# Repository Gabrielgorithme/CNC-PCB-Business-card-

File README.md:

# Hybrid business card: milled aluminium + PCB

The second version of Gabriel Ghanem's CNC business card. One half is milled from 7075 aluminium on a hobby CNC,
the other is a four-layer circuit board, and the two meet along a ripple that spreads from the card's flexure.

| | |
|---|---|
|  |  |

- Card: 85.60 x 53.98 x 1.70 mm, corners R3.18.
- Aluminium half: 7075, engraved both faces, with the same flexure as the first card.
- Board half: 1.2 mm, black mask, gold finish, castellated holes on the free edge. It carries an NFC tag
  (NT3H2111): a phone held to the card opens the website, and the phone's field lights a red LED behind a slot
  in the board. There is no battery.
- Joint: the board sits in a pocket on a narrow ledge, located by two pins milled from the solid, flush with the
  ripple crests.

## Where things are

| Folder | What it holds |
|---|---|
| `design/hybrid/` | The mockups that set the look. `concept_b2.py` is the chosen direction ("Wavefront"). |
| `pcb/revA/` | The board, generated by Python scripts as a KiCad project. `out/order/` is the package for the fab: Gerbers, BOM, placement. |
| `cad/hybrid/` | The aluminium half as a STEP model, generated with CadQuery from the same numbers as the board, plus the fit gauge and the drawing of the joint (`interface.png`). |
| `lettering/` | The single-line ISOCP letters, as engraved on the first card. |

Each folder has its own README with the details: geometry and checks for the board in `pcb/revA/`, how the board
is held and what gets machined to the delivered boards in `cad/hybrid/`.

## Status

Rev A. The board has been through an independent audit and a pre-order review; both are recorded in
`pcb/revA/README.md`. The aluminium pocket is cut to the measured thickness of the delivered boards
(`python3 cad/hybrid/build_alu.py --board-t <measured>`), so the aluminium half is finalised once boards are in hand.

## Rebuilding

- Mockups: `python3 design/hybrid/generate.py b2` (numpy, pillow, shapely, segno, `rsvg-convert`).
- Board: `pcb/revA/build.sh` (KiCad's Python module `pcbnew` and `kicad-cli`, shapely, numpy, pillow, scipy, CadQuery).
  A rebuild rewrites the Gerber zip with new time stamps even when nothing changed.
- Aluminium: `python3 cad/hybrid/build_alu.py` (CadQuery, svgelements; `--engrave` adds the engraved model).

## The first card

The first card (all aluminium) and the website both cards point to are in
[CNC-Business-card-](https://github.com/Gabrielgorithme/CNC-Business-card-). The QR code on both cards opens
https://gabrielgorithme.github.io/CNC-Business-card-/, which is served from that repository.

The history of this repository starts on that repository's branch `claude/hybrid-card-mockups`; the commits were
moved here unchanged on 2026-11-25.

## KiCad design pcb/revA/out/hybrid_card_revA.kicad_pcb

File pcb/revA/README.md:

# Hybrid card, PCB half, rev A

The board half of the B2 "Wavefront" card, generated from the same numbers as the mockup in `design/hybrid/`.
Rev A is ordered as the production batch (20 to 40 cards), not as a test coupon first: antenna tuning, the one thing
that cannot be settled on paper, is done by hand on the batch through the solder bridges.

## What is in `out/`

| File | What it is |
|---|---|
| `hybrid_card_revA.kicad_pcb` / `.kicad_pro` | The board. Written in KiCad 7's format, which KiCad 10 opens. |
| `gg_card.pretty/`, `fp-lib-table` | Project footprint library (the chip's footprint). |
| `hybrid_card_revA_board.step` | 3D model of the board with its parts, in the card's CAD frame (see below). For the assembly with the aluminium half. |
| `preview_front.jpg`, `preview_back.jpg`, `preview_front_lit.jpg` | Previews composited from KiCad's own layer plots. The back is shown as seen from the back. The lit view is a model, not a measurement. |
| `hybrid_card_revA_BOM_JLC.csv`, `..._CPL_JLC.csv` | Assembly files in JLCPCB's column layout (draft). |
| `order/` | What goes to JLCPCB: `hybrid_card_revA_gerbers.zip` (4 copper layers, masks, pastes, silkscreens, outline, one plated drill file: 87 x 0.3, 8 x 0.8, 2 x 2.1), the BOM and the placement file. Written by `make_order.py`. |
| `decal_front.jpg`, `decal_back.jpg` | The same pictures cropped exactly to the board's bounding box (43.565 x 47.42 mm, 54 px/mm), to lay on the 3D model's faces. The back one is as seen from the back. |

## Geometry shared with the aluminium half (card frame, mm, origin = card top-left seen from the recto)

- Flexure / ripple centre (19.0, 21.5). Joint on the 18th ripple crest, R36.
- Rims 3.18 top and bottom. Ledge 4.0 along the joint, 1.5 under the rims.
- Board outline drawn 0.10 smaller than the nominal pocket per side, R1.0 on the corners that sit in the pocket.
  The pocket is meant to be machined to the delivered boards.
- Two locating pins at R38, -24 deg and +22 deg: (53.71, 6.04) and (54.23, 35.74). Plated holes 2.10, lands 2.80.
- The free edge stops 0.10 inside the card's edge (x = 85.50).
- Copper to edge: on the back, along the joint and the rims, nothing closer than 0.50 (the pin lands). On the front the
  gold rings come to 0.36 and the edge fingers to 0.30 of the free edge.
- How the board sits on the aluminium (seat, glue land, pins, heights) is in `cad/hybrid/README.md`.

## The tag

NT3H2111 (NTAG I2C plus, 50 pF input capacitance, energy-harvesting output). VOUT feeds 220 nF, then 33 ohm and a red LED
(a standard top-emitting 0402 on the back). The resistor only matters in a strong field; 33 ohm is in JLCPCB's basic list.
Antenna: 7-turn rectangular spiral on the back, 14.1 x 29.2 mm, 0.20 track / 0.15 gap, placed against the board's free
edge, away from the aluminium. Calculated free-air inductance 2.10 uH (`coil.py`, Greenhouse method; expect about 10 % error).

It is deliberately tuned high. Three C0G capacitors sit behind solder bridges JP1..JP3: two bare pads 0.25 apart under one
mask opening, no paste. A blob of solder closes one; wick opens it again.

| Bridges closed | Added | Tunes this inductance to 13.56 MHz | Resonance if L = 2.10 uH |
|---|---|---|---|
| none | 0 pF | 2.65 uH | 15.2 MHz |
| JP1 | 6.8 pF | 2.34 uH | 14.3 MHz |
| JP2 | 12 pF | 2.15 uH | 13.7 MHz |
| JP1+JP2 | 18.8 pF | 1.95 uH | 13.1 MHz |
| JP3 | 22 pF | 1.86 uH | 12.8 MHz |
| JP1+JP3 | 28.8 pF | 1.70 uH | 12.2 MHz |
| JP2+JP3 | 34 pF | 1.60 uH | 11.8 MHz |
| all | 40.8 pF | 1.48 uH | 11.4 MHz |

Aluminium next to the coil lowers its inductance, so the right combination is found with the board seated in a pocket:
try the combinations and keep the one with the longest read range and brightest LED.

## Decorative copper

The BGA land pattern, fan-out, castellations, edge fingers, meanders and test points connect to nothing.
Each trace with the pads it touches is its own small net (`ART_1` ... `ART_68`), so the design-rule check treats them as
intended connections and still checks their clearances.

## Hidden under the ledge (back)

- Copper text at 0.5 / 0.6 / 0.7 / 0.8 / 1.0 mm and lines at 0.10 / 0.127 / 0.15 / 0.20 / 0.25 mm: a record of what this
  fab resolves, for the next board. Nothing on the board is under 0.10.

Nothing on the board is left to chance against the fab's limits any more: the antenna is fully under mask, and in the BGA
field the lands are gold while the dog-bone vias stay under mask on both faces, as on a real BGA: the gold neck of each
dog-bone stops at the via pad's edge, so the fab plugs all 49 holes and no mask web there is under 0.254.

## Vernier (back)

Eleven gold ticks 1.35 deg apart just outside the ledge's edge, facing eleven ticks 1.50 deg apart engraved on the aluminium.
One step of coincidence is 0.1 mm at R40.

## 3D model

`hybrid_card_revA_board.step` uses the same frame as `cad/build_card.py`: X along the long edge, Y up as seen from the
recto, origin at the card's bottom-left corner, Z = 0 the verso face, Z = 1.70 the faced recto. The board's top face
is at ripple-crest height, Z = 1.68; a 1.20 board occupies Z = 0.48 ... 1.68. Dropped into the card's assembly at the
origin it is in place.

The outline is rebuilt from true lines and arcs. Vias and copper are not modelled. Part bodies are plain blocks
(chip 1.6 x 1.6 x 0.5 from the datasheet; 0402 heights are nominal catalogue values).

## Thickness: 1.2 mm board

Card 1.70, board 1.20 nominal. The pocket is cut to the measured thickness of the delivered boards, so the top face
lands at crest height whatever the fab delivers (their tolerance is 10 %). The parts on the back are 0.50 tall:
with a 1.20 board their lowest face is 0.02 below the verso plane, plus the solder under them.
The stack-up in the board file is a nominal split that adds up to 1.20; the fab's standard 1.2 mm 4-layer stack-up applies.

## Checks done

- Design-rule check in KiCad 10.0.8 (through kicad-mcp-pro on the PC) and in KiCad 7: same result both times,
  0 unconnected items, 0 courtyard issues, 8 violations. All 8 are the castellated half-holes sitting on the
  board edge, which is what a castellated hole is.
- Rendered from the plots and looked at, front, back and lit.
- 3D model against KiCad's own STEP export of the board: same bounding box, same thickness, outline area equal to the
  board file's polygon to 0.01 mm2. Volumes differ by 7 mm3, which is the vias.
- Chip footprint against figs. 31 (outline) and 32 (reflow footprint) of the NT3H2111_2211 data sheet, rev 3.6, looked at as
  drawings: terminal order, land size and position, the wider pin 1 land and the bare centre all match. The paste is deliberately not the data sheet's: see the pre-order
  review below.
- Unused chip pins: SCL, SDA and FD are left open and VCC is not connected. NXP's support answers on their community
  forum say these may float when unused.
- Part numbers (JLCPCB parts library, looked up 2026-11-25): U1 C710403, D1 C130719 (NationStar NCD0402R1, red),
  R1 C25105 (33 ohm), C2 C16772 (220 nF X7R 16 V), C3 C1576 (6.8 pF C0G), C4 C1547 (12 pF C0G), C5 C1555 (22 pF C0G).
  Stock was not checked.

## Audit (2026-11-25)

An independent audit of the board file rebuilt the connectivity from the copper alone: all eight intended connections of
the tag circuit pass, no shorts, no opens, no closed copper loop over the coil on any layer, inductance confirmed at
2.09 to 2.10 uH by a second method. Its findings and what was done:

| Finding | Done |
|---|---|
| Placement angles were KiCad's raw bottom-side values; JLCPCB reads the bottom mirrored | `make_assembly.py` writes 180 minus KiCad's angle |
| No pin 1 mark for U1 on silk, D1's cathode dot too small to print | 0.4 dots beside U1 pin 1 and D1's cathode |
| Pin 1 land and paste of U1 not confirmed against the drawing | Redrawn from figs. 31 and 32 as seen: every land 0.40 x 0.22 at 0.60 from centre, the pin 1 land 0.32 wide with the extra 0.10 towards the corner. The 0.10 toe added earlier is gone. Paste: see the pre-order review |
| Castellations: 0.15 ring, first hole 2.32 from the corner | Pads 1.3 high (0.25 ring), row moved down 0.7 (3.02 from the corner) |
| A width clamp made every ladder line 0.15 | Ladders bypass the clamp |
| Mask webs under 0.254 at the pin lands and in the BGA field | Ring ends pulled back from the pin lands (0.3 web); dog-bone vias now under mask |
| 0.10 ring on the 49 dog-bone vias | 0.6 pads (0.15 ring) |
| "No copper within 0.6 of any edge" was not true | Statement corrected above |
| Solder bridges were 0402 lands with paste and a mask dam | Proper open solder bridges |
| "U1" label touched the layer-marker window | Moved |

## Pre-order review (2026-11-25)

A second pass by the same auditor on the order package and the JLCPCB cart, before payment. One blocking item, two cosmetic:

| Finding | Done |
|---|---|
| U1 paste apertures 0.35 x 0.17 (the data sheet's 0.025 pull-back): area ratio 0.57 with a 0.10 stencil, 0.48 with the 0.12 that JLCPCB pairs with 0402 and 0.5 pitch. Under the 0.66 guideline | Paste on the full land, 0.40 x 0.22 on all eight terminals (0.71 and 0.59), pin 1's at the nominal position with none on its extra strip |
| `JLCJLCJLCJLC` placeholder on silk: the auditor reads JLCPCB's help page as saying the order-number mark was withdrawn in 2026 and the placeholder should be left off; with "Remove Mark" it would print as written | Removed |
| The mask opening of each dog-bone ran to the via centre: 43 % of the hole open on the front, so neither plugged nor open | Opening ends at the via pad's edge; the 49 vias are covered on both faces |

Checked against the package uploaded before: only the back paste, back silk and front mask layers differ, and only at
those three places (rendered at 0.01 mm per pixel). Copper, outline and drill are identical.

## Before ordering

1. **Placement preview.** The angles are now converted for the bottom side, but JLCPCB also applies its own offset per
   library part. In their preview, U1's pin 1 must sit by the silk dot at (65.40, 42.80) and D1's cathode by the dot at
   (63.71, 37.90), card frame.
2. **Tooling holes.** Economic assembly may add tooling holes where JLCPCB chooses. Check that option, and the edge-rail
   option, at quote.
3. **LED direction.** A standard LED on the back shines away from the board. Whether enough light comes back into the
   slot off the phone is what this coupon tests.

## Order options this design assumes

| Option | Choice |
|---|---|
| Layers, thickness | 4 layers, 1.2 mm |
| Solder mask, finish | Black, ENIG |
| Castellated holes | Yes, 1 edge |
| Via covering | Plugged: the tented vias get filled, every hole with a mask opening stays open and gold |
| Outline tolerance | The precision option (+/-0.1) if offered |
| Mark on PCB (order number) | Remove Mark. No placeholder text on the board |
| Confirm production file / parts placement | Yes to both: this is where a rotated U1 or D1 gets caught |
| Assembly | Bottom side only; JP1..JP3 are not parts |
| Panel, rails, tooling holes | The curved edge and the castellated edge must stay clean. If the fab needs tabs or mouse-bites, ask for them on the two straight edges only (y = 3.28 and y = 50.70) |

## Rebuild

`./build.sh` (needs KiCad's Python module `pcbnew`, `kicad-cli`, shapely, numpy, scipy, pillow, `rsvg-convert`;
`make_step.py` needs CadQuery and runs without KiCad).

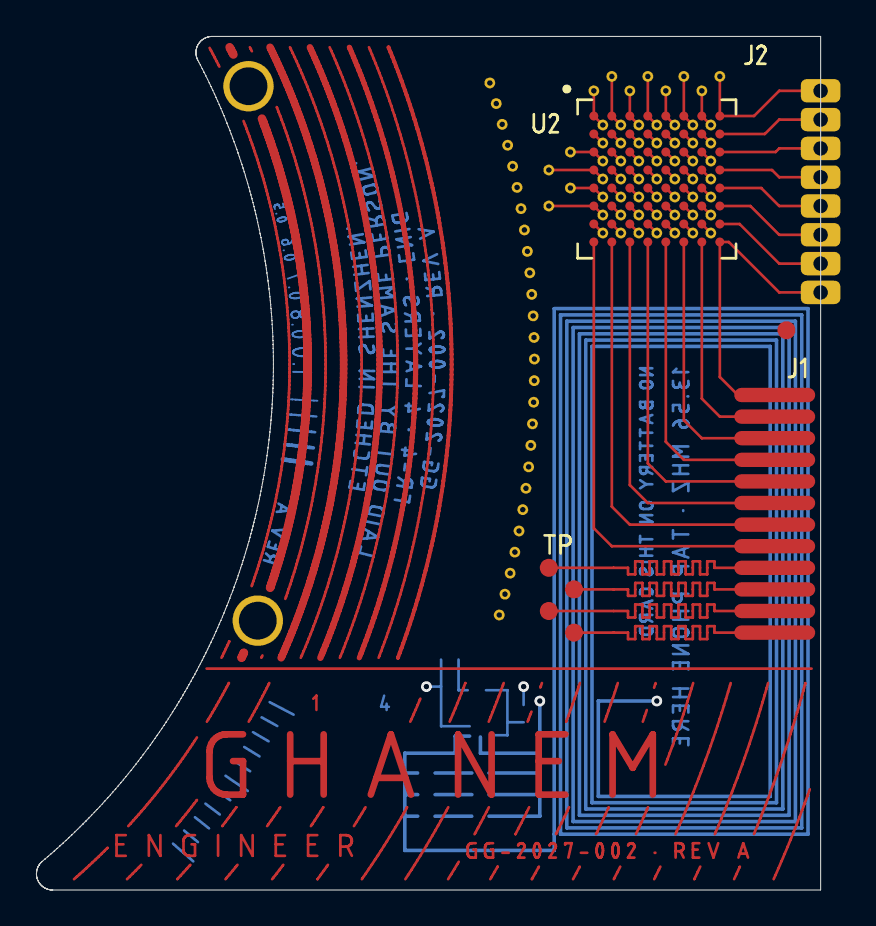
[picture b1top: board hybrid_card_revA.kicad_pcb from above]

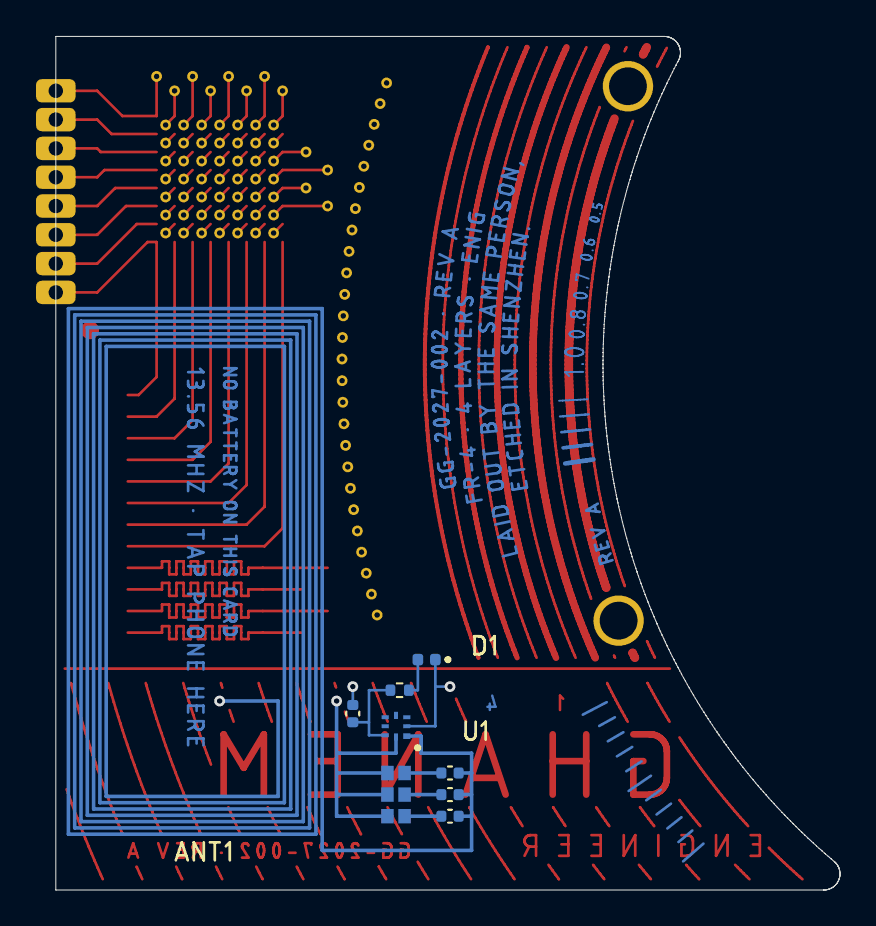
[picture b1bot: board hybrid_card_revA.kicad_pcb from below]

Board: 4 copper layers, 43.6 x 47.4 mm, 12 parts (11 on the bottom side), 76 nets.

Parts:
ANT1: 2.10uH_free_air_calc; ANT1_spiral_7T
ART1: decorative_pads_and_holes; ART_front
C2: 220n X7R 16V; C_0402_1005Metric
C3: 6.8p C0G; C_0402_1005Metric
C4: 12p C0G; C_0402_1005Metric
C5: 22p C0G; C_0402_1005Metric
D1: LED red 0402 NCD0402R1; LED_0402_1005Metric
JP1, JP2, JP3: solder bridge; SolderBridge_2_Pad0.7x0.8mm_Gap0.25mm
R1: 33R; R_0402_1005Metric
U1: NT3H2111W0FHK; XQFN-8_1.6x1.6mm_P0.5mm_SOT902-3

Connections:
ANT_A: ANT1.1, C3.1, C4.1, C5.1, U1.1
ANT_B: ANT1.2, JP1.2, JP2.2, JP3.2, U1.8
ART_1: ART1.29, ART1.93, ART1.142
ART_2: ART1.30, ART1.94, ART1.143
ART_3: ART1.31, ART1.95, ART1.144
ART_4: ART1.32, ART1.96, ART1.145
ART_5: ART1.33, ART1.97, ART1.146
ART_6: ART1.34, ART1.98, ART1.147
ART_7: ART1.35, ART1.99, ART1.148
ART_8: ART1.36, ART1.149, ART1.154
ART_9: ART1.37, ART1.100
ART_10: ART1.38, ART1.101
ART_11: ART1.39, ART1.102
ART_12: ART1.40, ART1.103
ART_13: ART1.41, ART1.104
ART_14: ART1.42, ART1.105
ART_15: ART1.43, ART1.106
ART_16: ART1.44, ART1.155
ART_17: ART1.45, ART1.107, ART1.150
ART_18: ART1.46, ART1.108
ART_19: ART1.47, ART1.109
ART_20: ART1.48, ART1.110
ART_21: ART1.49, ART1.111
ART_22: ART1.50, ART1.112
ART_23: ART1.51, ART1.113
ART_24: ART1.52, ART1.156
ART_25: ART1.53, ART1.114, ART1.151
ART_26: ART1.54, ART1.115
ART_27: ART1.55, ART1.116
ART_28: ART1.56, ART1.117
ART_29: ART1.57, ART1.118
ART_30: ART1.58, ART1.119
ART_31: ART1.59, ART1.120
ART_32: ART1.60, ART1.157
ART_33: ART1.61, ART1.121, ART1.152
ART_34: ART1.62, ART1.122
ART_35: ART1.63, ART1.123
ART_36: ART1.64, ART1.124
ART_37: ART1.65, ART1.125
ART_38: ART1.66, ART1.126
ART_39: ART1.67, ART1.127
ART_40: ART1.68, ART1.158
ART_41: ART1.69, ART1.128, ART1.153
ART_42: ART1.70, ART1.129
ART_43: ART1.71, ART1.130
ART_44: ART1.72, ART1.131
ART_45: ART1.73, ART1.132
ART_46: ART1.74, ART1.133
ART_47: ART1.75, ART1.134
ART_48: ART1.76, ART1.159
ART_49: ART1.77, ART1.135
ART_50: ART1.78, ART1.136
ART_51: ART1.79, ART1.137
ART_52: ART1.80, ART1.138
ART_53: ART1.81, ART1.139
ART_54: ART1.82, ART1.140
ART_55: ART1.83, ART1.141
ART_56: ART1.84, ART1.160
ART_57: ART1.85, ART1.169
ART_58: ART1.86, ART1.168
ART_59: ART1.87, ART1.167
ART_60: ART1.88, ART1.166
ART_61: ART1.89, ART1.165
ART_62: ART1.90, ART1.164
ART_63: ART1.91, ART1.163
ART_64: ART1.92, ART1.161, ART1.162
ART_65: ART1.170, ART1.171
ART_66: ART1.172, ART1.173
ART_67: ART1.174, ART1.175
ART_68: ART1.176, ART1.177
CT1: C3.2, JP1.1
CT2: C4.2, JP2.1
CT3: C5.2, JP3.1
GND: C2.2, D1.1, U1.2
LED_A: D1.2, R1.2
VOUT: C2.1, R1.1, U1.7
